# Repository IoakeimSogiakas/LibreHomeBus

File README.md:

## What’s New in Alpha

The project moves from Pre-Alpha to Alpha. The main change is that it now runs on a real RS-485 bus instead of a single board doing UART testing from Python.

Two CH32V003 nodes on a physical RS-485 bus, talking to a PC through a USB-RS485 dongle.
Discovery works on real hardware. Both nodes received unique addresses from the script.
The binary search is more forgiving of the timing on a real bus. A “no answer” now means three tries with no reply, and the result is checked afterwards: the lowest UID must answer and the number just below it must not. If the check fails, the search runs again.
Fixed CRC failures on the slave. Debug prints inside the frame polling loop were slow enough to corrupt frames on real RS-485. Per-frame logging is now behind a DEBUG_BUS switch in config.h, off by default.
Tested a switch (FID 1) driving a dimmer (FID 3) through both Home Assistant automations and ESPHome automations. The ESPHome version responds noticeably faster. The cause isn’t determined. The test setup has several hops (dongle, Windows, WSL, ESPHome host build, Home Assistant), and the extra latency might also be inherent to the Home Assistant path. This will be revisited with a real ESP master.
Scripts are being cut down. Only Descovery.py and bus_test.py will remain. bus_test.py is for bench testing nodes by hand.

## Why LibreHomeBus?

LibreHomeBus follows the architecture of professional centralized wired smart home systems like Loxone, but it is open source and costs far less.

Commercial setups can run to tens of thousands of dollars and often use proprietary bus encryption. In a home, fieldbus encryption adds little. To attack the bus, someone has to get into the house and open a wall. LibreHomeBus skips it in favor of simplicity, speed and low cost.

## 48V DC Room Topology 

A typical smart bulb contains its own AC-to-DC converter, so a house with fifty bulbs has fifty small mains power supplies. In cheap bulbs that converter sits right next to the LEDs in a sealed enclosure. The heat from the LEDs and the converter cooks its components, especially the electrolytic capacitors, and that is one of the most common ways LED bulbs fail.

LibreHomeBus does the AC-to-DC conversion once per room (or once per house) with a single power supply. That supply feeds a DC rail that runs next to the RS-485 data bus. Each node steps the rail down locally with a buck converter for the microcontroller and transceiver, and uses a dedicated LED driver for the light. The drivers sit apart from the LEDs, so the electronics stay cooler and last longer. Separating the driver from the LEDs is also common in good commercial lighting. This system just applies it throughout.

The rail is 48V for now, and the first prototype PCB will use it. It may change to 52V later. Earlier versions said 54V, and the power supply side is still untested, so treat the voltage as provisional.

A CH32V003 plus a proper LED driver makes a fixture with well-spaced, properly rated parts. The preliminary BOM for a custom SPI-based tunable white light is about €6.

*(Note: Schematics, BOMs, and Gerber files for the custom light fixtures and wall switches will be published in this repository as the hardware phase of the project matures.)*

---

# Project Status: Alpha

The firmware and discovery script work on a physical RS-485 bus with two nodes. This is still a prototype, and cleanup and refactoring are ongoing.

### Important Notes
* **Test setup:** Development is done with the ESPHome host build running in WSL, with the USB-RS485 dongle passed through with usbipd. A real ESP master hasn’t been tested yet.

* **Bus size:** Discovery has only been tested with two nodes. Larger multi-node buses are untested.

* **Scripts:** Two scripts remain in tools/. Descovery.py finds nodes, assigns addresses and writes a basic hub.yaml for ESPHome. bus_test.py is a menu for bench testing (read and write registers, on/off checks, identify LED test, watch a register, forget a node by UID). They work and can be used as they are, but they’re clunky. Settings like the serial port and ESPHome target are constants at the top of each file, and there is no command-line interface. A proper commissioning flow and a graphical interface are planned for the future.
* **Changing addresses:** There’s no separate script for it. Use the “forget a node by UID” option in bus_test.py to clear a node’s saved address, then run discovery again. Discovery picks the lowest free address, and you can’t choose one yourself yet. (I will probably add a way in the bus_test skript if I find a need for that)
* **ESPHome config generation:** Basic generation works for FID 1, 2, 3, 5 and 6. FID 4 has no YAML mapping yet and is skipped. Node identification and automation coupling are planned. See Future Plans.
* **PCB testing:** Not started. Everything so far runs on dev boards and breadboards. See Future Plans.

---

## Flavor Status

| FID | Personality | Registers Used | Interface | Status |
|:---:|:---|:---|:---|:---:|
| 1 | Toggle Switch Input | Reg 1 (State, read-only), Reg 2 (Identify LED) | Digital input, debounced with internal pull-up, PCB LED | RS-485 bus tested, LED bench tested |
| 2 | Relay / On-Off Light | Reg 1 (On/Off) | Push-pull digital output | RS-485 bus tested |
| 3 | Single-Channel Dimmer | Reg 1 (On/Off), Reg 2 (0..1000) | TIM1 CH1 PWM at 48 kHz | RS-485 bus tested |
| 4 | Tunable White (SPI) | Pending | Dedicated SPI driver IC | Pending |
| 5 | Tunable White (Dual PWM) | Reg 1 (On/Off), Reg 2 (Cold), Reg 3 (Warm) | TIM1 CH1 + CH3 PWM at 1 kHz | Bench tested |
| 6 | Wall Plug | Reg 1 (On/Off), Reg 2 (Identify LED) | Relay output, local toggle switch (no register), PCB LED | RS-485 bus tested |

Register 0 always holds the FID and is read-only. The identify LED register is only written by the commissioning script, and the node turns the LED off by itself after 30 s.

FID 4 is planned for bench testing next.

---

## Architecture & Hardware

```text
[ Home Assistant ]
       |
       |  Native API (Wi-Fi or Ethernet)
       v
[ ESPHome Master ] (ESP32 / ESP8266)
       |
       |  Modbus RTU (115200 baud, UART + DE/RE direction pin)
       v
======= RS-485 Bus ==============================================
       |                         |                         |
 [ CH32V003 Node ]         [ CH32V003 Node ]         [ CH32V003 Node ]
 Flavor 1 (Switch)         Flavor 2 (Relay)          Flavor 5 (TW Light)
==================================================================

```
---

### Why ESPHome as the Master?

Home Assistant's native Modbus integration relies on polling loops that are too sluggish for wall switches. Running the bus master on an ESP via ESPHome allows continuous, low-latency polling directly over the hardware UART. Input changes trigger immediate state pushes to Home Assistant over the native API.

### Hardware Notes
* **Transceivers & Voltage:** The system is currently designed and bench-tested around a **5V logic level** using the SN65HVD3082E RS-485 transceiver. Any standard 3.3V or 5V transceiver (MAX485, clones, isolated modules) is compatible, provided the logic levels match your supply rail.
* **Node Connections:** The CH32V003 slave firmware uses `PD5` for TX, `PD6` for RX, and `PD4` to control the transceiver's DE and /RE lines tied together.
* **Master Connections & Level Shifting:** The ESP requires three pins wired to its transceiver: UART TX, UART RX, and a GPIO driving DE and /RE. Since **all ESP32 and ESP8266 microcontrollers use 3.3V logic** (including ethernet gateways like the WT32-ETH01), if you are pairing the ESP with a 5V transceiver, you must step down the transceiver's 5V RX output to the ESP's 3.3V RX input using a simple voltage divider (e.g., a 2kΩ and 1kΩ resistor pair).

---

## Commissioning Protocol

New or unassigned nodes run with address 0 (`DEFAULT_ID = 0`). The discovery script uses a binary search across the 64-bit factory UID space, following a model similar to DALI commissioning:

1. **Compare (`0x41`):** The master broadcasts a UID threshold. Any unassigned node whose factory UID is less than or equal to that number answers with a single confirmation byte (`0x55`).

2. **Binary Search:** By halving the 64-bit UID search window based on whether anyone answers, the master isolates the lowest UID on the bus in roughly 64 queries.

3. **Assign Address (`0x42`):** Once a single chip is isolated, the master sends a broadcast command with that specific UID and its new address (1–247).

4. **Flash Storage:** The chip writes the new address into its last 64-byte flash page (`0x08003FC0`), so the address survives reboots and firmware reflashes.

5. **Clear / Reset (`0x43`):** Broadcast command that tells a specific UID to erase its saved address and revert to unassigned mode.

6. **Identification LED (switch and plug only):** The switch (FID 1) and plug (FID 6) flavors have an LED on `PC2`, controlled by register 2. Once a node has an address, the master can turn the LED on with a normal write (function `0x06`) so you can see which physical device got which address. It turns itself off after 30 seconds if the master forgets. The current discovery script doesn't use it yet, it's there for a later version.

---

## Future Plans
* **Node identification:** Before naming a node, the script asks which physical device it is. It uses the identify register on flavors that have one. On lights it can turn the light on.
* **Automation coupling:** Link inputs to outputs from the script, for example a switch to a specific light.
* **Better ESPHome YAML generation:** Read the discovered flavors, map the registers, and write a ready-to-flash config.
* **Caching:** The script will cache what it learns (for example the addresses, UIDs and flavors of nodes it has already found) so later runs are faster and don’t repeat the full discovery.
* **Real ESP master:** Move off the WSL host build and recheck latency, including the Home Assistant path. (this will probally happen in the next week)
* **PCB testing:** Prototype boards on the 48V rail. Planned for a few months from now.

## Licensing

This project is dual-licensed to cover both hardware designs and software/firmware components:

* **Firmware & Software Tools:** Licensed under [GNU General Public License v3.0 (GPL-3.0)](LICENSE).
* **Hardware (KiCad Schematics, PCB Layouts, & Libraries):** Licensed under [CERN-OHL-S v2 (Strong Reciprocal)](LICENSE-HARDWARE).

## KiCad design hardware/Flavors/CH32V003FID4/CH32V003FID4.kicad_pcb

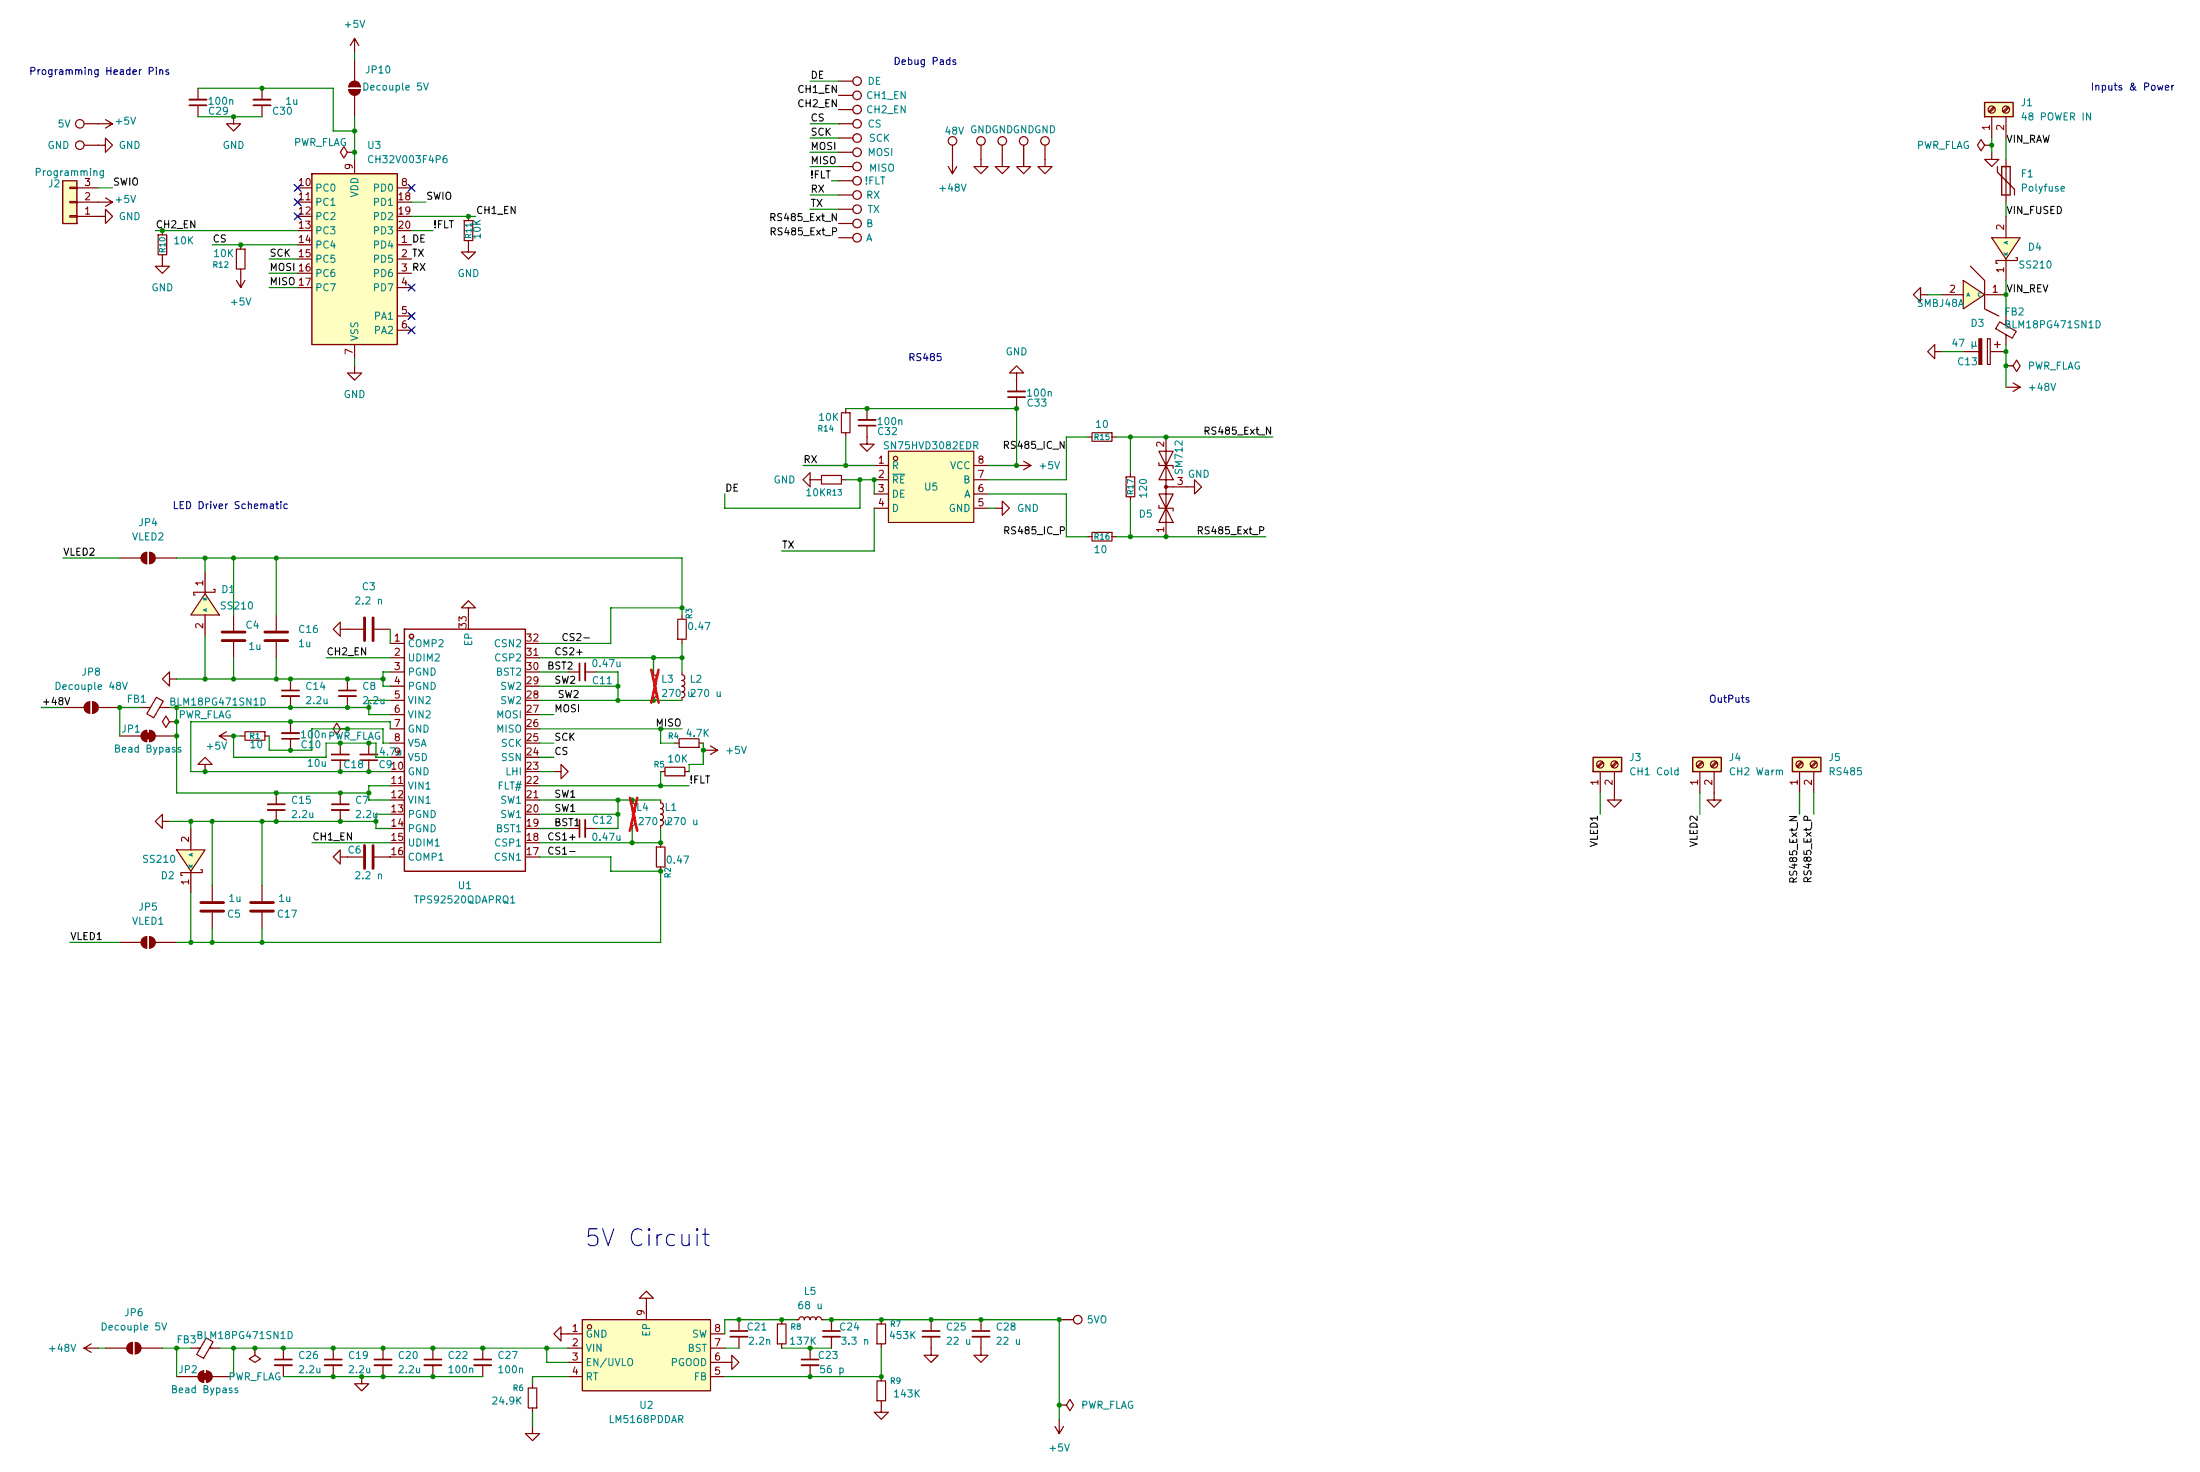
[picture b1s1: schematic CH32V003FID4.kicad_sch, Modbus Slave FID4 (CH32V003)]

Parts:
C3, C6: 2.2 n; C_1206_3216Metric
C4, C5, C16, C17, C30: 1u; C_1206_3216Metric
C7, C8, C14, C15, C19, C20, C26: 2.2u; C_1206_3216Metric
C9: 4.7u; C_1206_3216Metric
C10, C22, C27, C29, C32, C33: 100n; C_1206_3216Metric
C11, C12: 0.47u; C_1206_3216Metric
C13: 47 µ; CP_Elec_10x10.5
C18: 10u; C_1206_3216Metric
C21: 2.2n; C_1206_3216Metric
C23: 56 p; C_1206_3216Metric
C24: 3.3 n; C_1206_3216Metric
C25, C28: 22 u; C_1206_3216Metric
D1, D2, D4: SS210; D_SMA; MPN SS210; LCSC Part C14996
D3: SMBJ48A; SMB_L4.6-W3.6-LS5.3-RD; MPN SMBJ48A; LCSC Part C353356
D5: SM712; SOT-23; LCSC C5199207
F1: Polyfuse; Fuse_1812_4532Metric
FB1, FB2, FB3: BLM18PG471SN1D; L_0603_1608Metric
J1: 48 POWER IN; TerminalBlock_Phoenix_MKDS-1,5-2_1x02_P5.00mm_Horizontal
J2: Programming; PinHeader_1x03_P2.54mm_Vertical
J3: CH1 Cold; TerminalBlock_Phoenix_MKDS-1,5-2_1x02_P5.00mm_Horizontal
J4: CH2 Warm; TerminalBlock_Phoenix_MKDS-1,5-2_1x02_P5.00mm_Horizontal
J5: RS485; TerminalBlock_Phoenix_MKDS-1,5-2_1x02_P5.00mm_Horizontal
JP1, JP2: Bead Bypass; SolderJumper-2_P1.3mm_Bridged_RoundedPad1.0x1.5mm
JP4: VLED2; SolderJumper-2_P1.3mm_Open_RoundedPad1.0x1.5mm
JP5: VLED1; SolderJumper-2_P1.3mm_Open_RoundedPad1.0x1.5mm
JP6, JP10: Decouple 5V; SolderJumper-2_P1.3mm_Open_RoundedPad1.0x1.5mm
JP8: Decouple 48V; SolderJumper-2_P1.3mm_Open_RoundedPad1.0x1.5mm
L1, L2: 270 u; L_10.4x10.4_H4.8
L3, L4: 270 u; L_Bourns_SRR1260; not fitted
L5: 68 u; L_APV_ANR4020
R1, R15, R16: 10; R_0805_2012Metric
R2, R3: 0.47; R_0805_2012Metric
R4: 4.7K; R_0805_2012Metric
R5, R10, R11, R12, R13, R14: 10K; R_0805_2012Metric
R6: 24.9K; R_0805_2012Metric
R7: 453K; R_0805_2012Metric
R8: 137K; R_0805_2012Metric
R9: 143K; R_0805_2012Metric
R17: 120; R_0805_2012Metric
TP2: 5V; TestPoint_Pad_D1.5mm
TP3, TP12, TP13, TP14, TP15: GND; TestPoint_Pad_D1.5mm
TP4: CH2_EN; TestPoint_Pad_D1.5mm
TP5: CS; TestPoint_Pad_D1.5mm
TP6: SCK; TestPoint_Pad_D1.5mm
TP7: MOSI; TestPoint_Pad_D1.5mm
TP8: MISO; TestPoint_Pad_D1.5mm
TP9: CH1_EN; TestPoint_Pad_D1.5mm
TP10: !FLT; TestPoint_Pad_D1.5mm
TP11: 48V; TestPoint_Pad_D1.5mm
TP19: 5VO; TestPoint_Pad_D1.5mm
TP20: DE; TestPoint_Pad_D1.5mm
TP21: RX; TestPoint_Pad_D1.5mm
TP22: TX; TestPoint_Pad_D1.5mm
TP23: B; TestPoint_Pad_D1.5mm
TP24: A; TestPoint_Pad_D1.5mm
U1: TPS92520QDAPRQ1; MPN TPS92520QDAPRQ1; LCSC C3191125
U2: LM5168PDDAR; MPN LM5168PDDAR; LCSC Part C5751958
U3: CH32V003F4P6; TSSOP-20_4.4x6.5mm_P0.65mm; MPN CH32V003F4P6; LCSC C5187096
U5: SN75HVD3082EDR; MPN SN75HVD3082EDR; LCSC Part C140254

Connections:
+5V: C9.2, C18.2, C24.1, C25.1, C28.1, C32.2, C33.1, J2.2, JP10.2 (B), L5.2, R1.2, R4.1, R5.1, R7.2, R12.2, R14.1, TP2.1 (1_1), TP19.1 (1_1), U1.9 (V5D), U5.8 (VCC)
+48V: C13.1, FB2.2, JP6.1 (A), JP8.1 (A), TP11.1 (1_1)
/!FLT: R5.2, TP10.1 (1_1), U1.22 (FLT#), U3.20 (PD3)
/BST1: C12.1, U1.19 (BST1)
/BST2: C11.1, U1.30 (BST2)
/CH1_EN: R11.1, TP9.1 (1_1), U1.15 (UDIM1), U3.19 (PD2)
/CH2_EN: R10.1, TP4.1 (1_1), U1.2 (UDIM2), U3.13 (PC3)
/CS: R12.1, TP5.1, U1.24 (SSN), U3.14 (PC4)
/CS1+: L1.1, L4.1, R2.1, U1.18 (CSP1)
/CS1-: C5.1, C17.1, D2.1 (K), JP5.2 (B), R2.2, U1.17 (CSN1)
/CS2+: L2.1, L3.1, R3.1, U1.31 (CSP2)
/CS2-: C4.1, C16.1, D1.1 (K), JP4.2 (B), R3.2, U1.32 (CSN2)
/DE: R13.2, TP20.1 (1_1), U3.1 (PD4), U5.2 (~RE), U5.3 (DE)
/MISO: R4.2, TP8.1, U1.26 (MISO), U3.17 (PC7)
/MOSI: TP7.1, U1.27 (MOSI), U3.16 (PC6)
/RS485_Ext_N: D5.2 (A2), J5.1, R15.1, R17.1, TP23.1 (1_1)
/RS485_Ext_P: D5.1 (A1), J5.2, R16.1, R17.2, TP24.1 (1_1)
/RS485_IC_N: R15.2, U5.7 (B)
/RS485_IC_P: R16.2, U5.6 (A)
/RX: R14.2, TP21.1 (1_1), U3.3 (PD6), U5.1 (R)
/SCK: TP6.1, U1.25 (SCK), U3.15 (PC5)
/SW1: C12.2, L1.2, L4.2, U1.20 (SW1), U1.21 (SW1)
/SW2: C11.2, L2.2, L3.2, U1.28 (SW2), U1.29 (SW2)
/SWIO: J2.3, U3.18 (PD1)
/TX: TP22.1 (1_1), U3.2 (PD5), U5.4 (D)
/VIN_FUSED: D4.2 (A), F1.2
/VIN_RAW: F1.1, J1.2
/VIN_REV: D3.1 (C), D4.1 (K), FB2.1
/VLED1: J3.1, JP5.1 (A)
/VLED2: J4.1, JP4.1 (A)
GND: C3.1, C4.2, C5.2, C6.1, C7.2, C8.1, C9.1, C10.2, C13.2, C14.1, C15.2, C16.2, C17.2, C18.1, C19.2, C20.2, C22.2, C25.2, C26.2, C27.2, C28.2, C29.1, C30.1, C32.1, C33.2, D1.2 (A), D2.2 (A), D3.2 (A), D5.3 (common), J1.1, J2.1, J3.2, J4.2, R6.1, R9.1, R10.2, R11.2, R13.1, TP3.1 (1_1), TP12.1 (1_1), TP13.1 (1_1), TP14.1 (1_1), TP15.1 (1_1), U1.3 (PGND), U1.4 (PGND), U1.7 (GND), U1.10 (GND), U1.13 (PGND), U1.14 (PGND), U1.23 (LHI), U1.33 (EP), U2.1 (GND), U2.6 (PGOOD), U2.9 (EP), U3.7 (VSS), U5.5 (GND)
unnamed: C23.1, C24.2, R8.1
unnamed: FB1.1, JP1.1 (A), JP8.2 (B)
unnamed: C7.1, C8.2, C14.2, C15.1, FB1.2, JP1.2 (B), U1.5 (VIN2), U1.6 (VIN2), U1.11 (VIN1), U1.12 (VIN1)
unnamed: FB3.1, JP2.1 (A), JP6.2 (B)
unnamed: C19.1, C20.1, C22.1, C26.1, C27.1, FB3.2, JP2.2 (B), U2.2 (VIN), U2.3 (EN/UVLO)
unnamed: C29.2, C30.2, JP10.1 (A), U3.9 (VDD)
unnamed: C6.2, U1.16 (COMP1)
unnamed: C3.2, U1.1 (COMP2)
unnamed: C10.1, R1.1, U1.8 (V5A)
unnamed: C21.2, U2.7 (BST)
unnamed: C23.2, R7.1, R9.2, U2.5 (FB)
unnamed: R6.2, U2.4 (RT)
unnamed: C21.1, L5.1, R8.2, U2.8 (SW)

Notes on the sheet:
RS485
5V Circuit
Inputs & Power
Programming Header Pins
Debug Pads
LED Driver Schematic
OutPuts

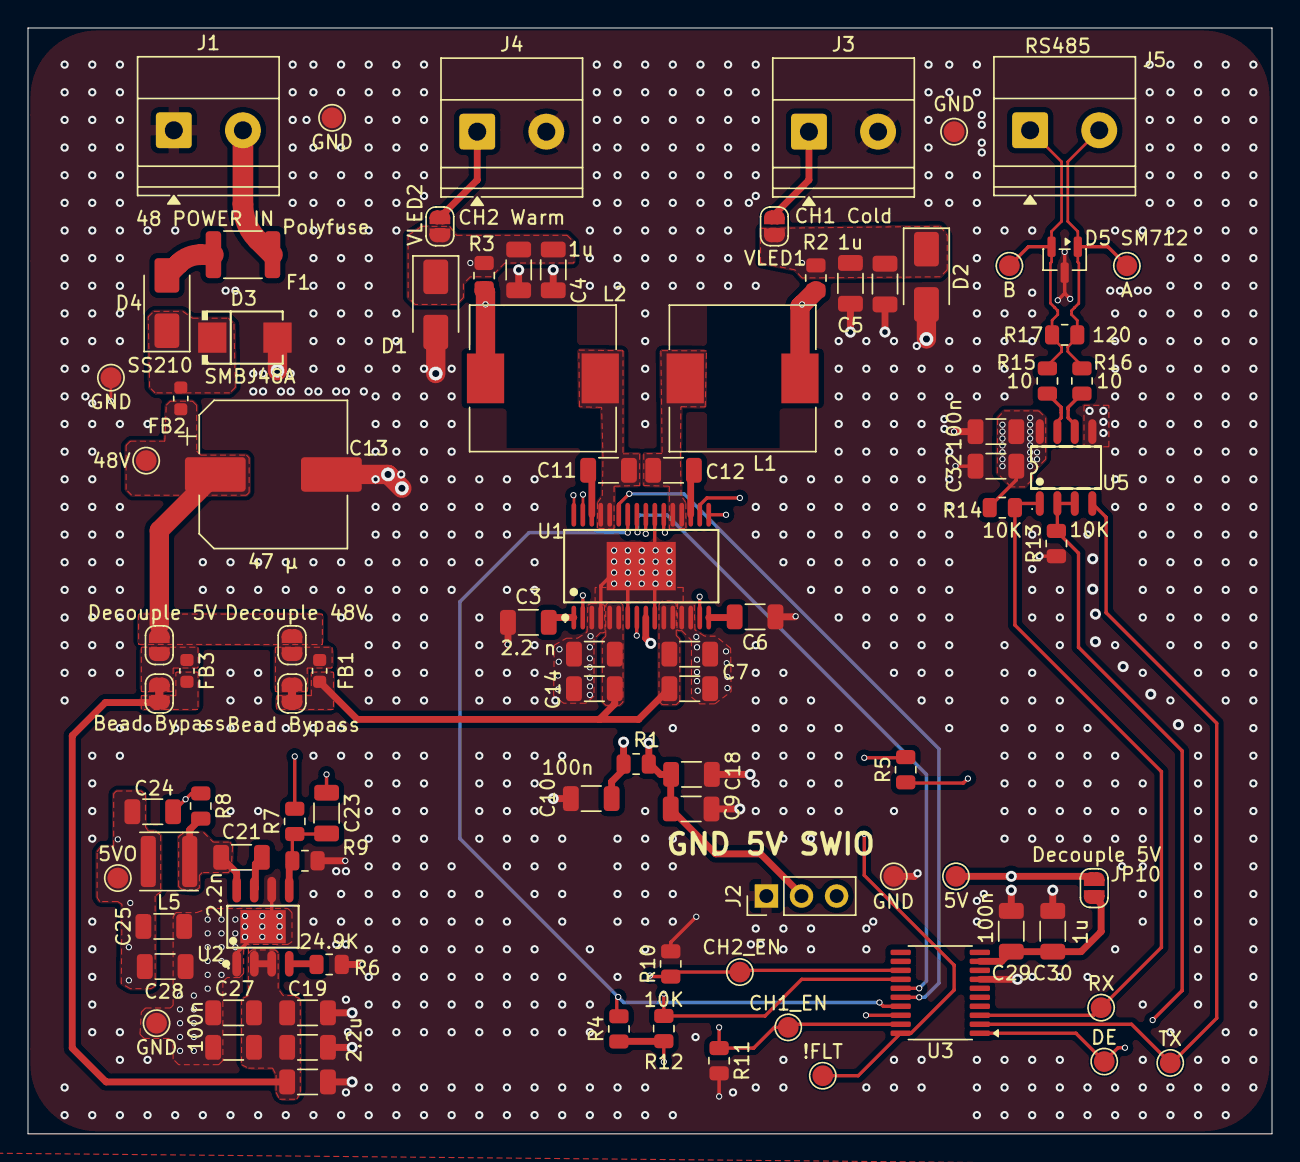
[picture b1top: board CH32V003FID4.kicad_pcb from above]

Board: 4 copper layers, 90.0 x 80.0 mm, 91 parts (0 on the bottom side), 44 nets.

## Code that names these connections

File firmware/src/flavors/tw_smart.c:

/*
 * FID 4: tunable white on a TPS92520-Q1. Same registers as FID 5.
 *   reg 1: on/off
 *   reg 2: cold 0..1000  (TPS channel 1)
 *   reg 3: warm 0..1000  (TPS channel 2)
 *
 * IADJ sets the LED current once at init, brightness is the TPS internal
 * PWM. CHx_EN drive UDIM and hard-gate each channel.
 *
 * Every pass sends at most one SPI frame (a read is two, ~50 us) so the
 * UART never misses a byte. Only tps_init() blocks longer (~1 ms).
 */

#include "node.h"
#include "tps92520.h"

#if FLAVOR == FID_TW_SMART

#define CH1_EN_PIN    PD2      /* UDIM1, cold */
#define CH2_EN_PIN    PC3      /* UDIM2, warm */
#define FLT_PIN       PD3      /* !FLT, open drain, active low */

#define RCS_MOHM      470      /* R2/R3, milliohm. Must match the board */
#define LED_MA        340      /* LED current per channel */
#define TON           7        /* ~437 kHz switching */
#define PWMDIV        0        /* 1507 Hz PWM */

#define REG_ONOFF     1
#define REG_COLD      2
#define REG_WARM      3
#define LEVEL_MAX     1000

#define STATUS_MS     200
#define RETRY_MS      500

/* I_LED = 2.45 V * IADJ / 1024 / (14 * Rcs) */
#define IADJ  ((LED_MA * 14ULL * RCS_MOHM * 1024 + 1225000) / 2450000)

#if IADJ > 1023
#error "LED_MA is above what RCS_MOHM allows"
#endif
#if LED_MA > 1600
#error "TPS92520 is rated 1.6 A per channel"
#endif

static const uint8_t en_pin[2]  = { CH1_EN_PIN, CH2_EN_PIN };
static const uint8_t pwm_l[2]   = { TPS_CH1PWML, TPS_CH2PWML };
static const uint8_t pwm_h[2]   = { TPS_CH1PWMH, TPS_CH2PWMH };

static uint8_t  ready;
static uint16_t cur[2];        /* duty the TPS has */
static uint8_t  step[2];       /* 0 idle, 1 high byte sent */
static uint16_t next[2];
static uint8_t  st_step;
static uint8_t  last_s1, last_s2, last_tw;
static uint32_t t_status, t_retry;

static uint16_t duty(uint16_t level)
{
    return (uint16_t)(((uint32_t)level * TPS_PWM_MAX + LEVEL_MAX / 2) / LEVEL_MAX);
}

static void stop(void)
{
    funDigitalWrite(CH1_EN_PIN, FUN_LOW);
    funDigitalWrite(CH2_EN_PIN, FUN_LOW);
    ready = 0;
    t_retry = SysTick->CNT;
}

static void start(void)
{
    if (!tps_init(IADJ, IADJ, TON, PWMDIV)) {
        t_retry = SysTick->CNT;
        return;
    }
    ready = 1;
    cur[0] = cur[1] = 0;
    step[0] = step[1] = 0;
    st_step = 0;
    t_status = SysTick->CNT;
    debugln("tps ready, iadj %u", (unsigned)IADJ);
}

/* One SPI frame per call. Returns 1 if it used the bus. */
static int channel_poll(int ch, uint16_t want)
{
    if (step[ch] == 0) {
        if (want == cur[ch]) return 0;
        if (want == 0) funDigitalWrite(en_pin[ch], FUN_LOW);
        next[ch] = want;
        tps_write(pwm_h[ch], next[ch] >> 8);
        step[ch] = 1;
        return 1;
    }
    tps_write(pwm_l[ch], next[ch] & 0xFF);     /* low byte latches the value */
    cur[ch] = next[ch];
    step[ch] = 0;
    if (cur[ch]) funDigitalWrite(en_pin[ch], FUN_HIGH);
    return 1;
}

static void status_poll(void)
{
    int v;

    switch (st_step) {
    case 0:
        if ((uint32_t)(SysTick->CNT - t_status) < STATUS_MS * DELAY_MS_TIME) return;
        t_status = SysTick->CNT;
        v = tps_read(TPS_STATUS3);
        if (v < 0 || (v & (TPS_STANDALONE | TPS_PC | TPS_CMWTO))) {
            debugln("tps lost (status3 %d), restarting", v);
            stop();
            return;
        }
        if (!!(v & TPS_TW) != last_tw) {
            last_tw = !!(v & TPS_TW);
            debugln("tps thermal warning %s", last_tw ? "on" : "off");
        }
        if ((v & (TPS_CH1STATUS | TPS_CH2STATUS)) || !funDigitalRead(FLT_PIN)) {
            st_step = 1;
        }
        return;
    case 1:
        v = tps_read(TPS_STATUS1);
        if (v >= 0 && v != last_s1) {
            last_s1 = v;
            debugln("tps status1 %02X", v);
        }
        st_step = 2;
        return;
    case 2:
        v = tps_read(TPS_STATUS2);
        if (v >= 0 && v != last_s2) {
            last_s2 = v;
            debugln("tps status2 %02X", v);
        }
        st_step = 3;
        return;
    default:
        tps_write(TPS_SYSCFG1, TPS_CMWEN | TPS_CH1INTPWM | TPS_CH1EN |
                               TPS_CH2INTPWM | TPS_CH2EN | TPS_FPINRST);
        st_step = 0;
        return;
    }
}

void flavor_init(void)
{
    funPinMode(CH1_EN_PIN, GPIO_CFGLR_OUT_10Mhz_PP);
    funPinMode(CH2_EN_PIN, GPIO_CFGLR_OUT_10Mhz_PP);
    funDigitalWrite(CH1_EN_PIN, FUN_LOW);
    funDigitalWrite(CH2_EN_PIN, FUN_LOW);
    funPinMode(FLT_PIN, GPIO_CFGLR_IN_PUPD);
    funDigitalWrite(FLT_PIN, FUN_HIGH);

    regs[REG_ONOFF] = 0;
    regs[REG_COLD]  = LEVEL_MAX;
    regs[REG_WARM]  = LEVEL_MAX;
    reg_max[REG_ONOFF] = 1;
    reg_max[REG_COLD]  = LEVEL_MAX;
    reg_max[REG_WARM]  = LEVEL_MAX;

    tps_spi_init();
    start();            /* must run within ~1.5 s of TPS power-up */
}

void flavor_poll(void)
{
    if (!ready) {
        /* tps_init blocks ~1 ms, don't start it while a frame is coming in */
        if (rx_len == 0 &&
            (uint32_t)(SysTick->CNT - t_retry) > RETRY_MS * DELAY_MS_TIME) {
            start();
        }
        return;
    }

    uint16_t on = regs[REG_ONOFF];
    uint16_t want0 = on ? duty(regs[REG_COLD]) : 0;
    uint16_t want1 = on ? duty(regs[REG_WARM]) : 0;

    if (step[1] == 0 && channel_poll(0, want0)) return;
    if (channel_poll(1, want1)) return;
    status_poll();
}

#endif /* FLAVOR == FID_TW_SMART */

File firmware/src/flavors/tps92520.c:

/*
 * TPS92520-Q1 dual buck LED driver over SPI1.
 *
 * Frame (16 bit, MSB first, mode 0):  CMD | A5..A0 | PAR | D7..D0
 *   CMD 1 = write, PAR makes the number of 1s odd.
 * The reply to a frame comes back during the next one.
 */

#include "tps92520.h"

#if FLAVOR == FID_TW_SMART

#define CS_PIN     PC4
#define SCK_PIN    PC5
#define MOSI_PIN   PC6
#define MISO_PIN   PC7      /* open drain on the TPS side, needs a pull-up */

/* 48 MHz / 64 = 750 kHz. Datasheet max is 2 MHz; MISO rises through the
 * pull-up, so leave margin. */
#define SPI_DIV    SPI_BaudRatePrescaler_64

#define RD_MASK    0xFC00   /* SPE + the fixed 11000 field */
#define RD_OK      0x6000

void tps_spi_init(void)
{
    RCC->APB2PCENR |= RCC_APB2Periph_SPI1;

    funPinMode(CS_PIN, GPIO_CFGLR_OUT_10Mhz_PP);
    funDigitalWrite(CS_PIN, FUN_HIGH);
    funPinMode(SCK_PIN, GPIO_CFGLR_OUT_10Mhz_AF_PP);
    funPinMode(MOSI_PIN, GPIO_CFGLR_OUT_10Mhz_AF_PP);
    funPinMode(MISO_PIN, GPIO_CFGLR_IN_PUPD);
    funDigitalWrite(MISO_PIN, FUN_HIGH);

    SPI1->CTLR1 = SPI_Direction_2Lines_FullDuplex | SPI_Mode_Master |
                  SPI_DataSize_16b | SPI_CPOL_Low | SPI_CPHA_1Edge |
                  SPI_NSS_Soft | SPI_DIV | SPI_FirstBit_MSB;
    SPI1->CTLR1 |= CTLR1_SPE_Set;
}

static uint16_t xfer(uint16_t out)
{
    funDigitalWrite(CS_PIN, FUN_LOW);
    Delay_Us(1);
    (void)SPI1->DATAR;
    while (!(SPI1->STATR & SPI_STATR_TXE));
    SPI1->DATAR = out;
    while (!(SPI1->STATR & SPI_STATR_RXNE));
    uint16_t in = SPI1->DATAR;
    while (SPI1->STATR & SPI_STATR_BSY);
    Delay_Us(1);
    funDigitalWrite(CS_PIN, FUN_HIGH);
    Delay_Us(2);
    return in;
}

static uint16_t frame(uint8_t wr, uint8_t addr, uint8_t data)
{
    uint16_t f = ((uint16_t)(wr ? 1 : 0) << 15) | ((uint16_t)(addr & 0x3F) << 9) | data;
    uint16_t p = f;
    p ^= p >> 8;
    p ^= p >> 4;
    p ^= p >> 2;
    p ^= p >> 1;
    if (!(p & 1)) f |= 1u << 8;
    return f;
}

int tps_read(uint8_t addr)
{
    xfer(frame(0, addr, 0));
    uint16_t r = xfer(frame(0, TPS_SYSCFG1, 0));
    if ((r & RD_MASK) != RD_OK) return -1;
    return r & 0xFF;
}

void tps_write(uint8_t addr, uint8_t data)
{
    xfer(frame(1, addr, data));
}

/* Write, then check the echo the TPS sends back in the next frame. */
static int write_check(uint8_t addr, uint8_t data)
{
    uint16_t f = frame(1, addr, data);
    xfer(f);
    uint16_t r = xfer(frame(0, TPS_SYSCFG1, 0));
    uint16_t want = ((f >> 1) & 0x7F00) | data;
    return r == want;
}

static int write_iadj(uint8_t reg_l, uint16_t v)
{
    return write_check(reg_l + 1, v >> 2) && write_check(reg_l, v & 3);
}

int tps_init(uint16_t iadj1, uint16_t iadj2, uint8_t ton, uint8_t pwmdiv)
{
    const uint8_t run = TPS_CMWEN | TPS_CH1INTPWM | TPS_CH1EN | TPS_CH2INTPWM | TPS_CH2EN;

    int s3 = tps_read(TPS_STATUS3);
    if (s3 < 0) {
        s3 = tps_read(TPS_STATUS3);     /* TPS may still be coming out of POR */
        if (s3 < 0) return 0;
    }
    if (s3 & TPS_STANDALONE) {
        tps_write(TPS_RESET, 0xC3);
        if (tps_read(TPS_STATUS3) < 0) return 0;
    }

    if (iadj1 > 1023) iadj1 = 1023;
    if (iadj2 > 1023) iadj2 = 1023;

    return write_check(TPS_SYSCFG1, TPS_CMWEN) &&
           write_check(TPS_SYSCFG2, 0) &&
           write_check(TPS_PWMDIV, pwmdiv) &&
           write_check(TPS_CH1TON, ton) &&
           write_check(TPS_CH2TON, ton) &&
           write_iadj(TPS_CH1IADJL, iadj1) &&
           write_iadj(TPS_CH2IADJL, iadj2) &&
           write_check(TPS_CH1PWMH, 0) && write_check(TPS_CH1PWML, 0) &&
           write_check(TPS_CH2PWMH, 0) && write_check(TPS_CH2PWML, 0) &&
           write_check(TPS_LHCFG1, 0) &&
           write_check(TPS_SYSCFG1, run) &&
           (tps_write(TPS_SYSCFG1, run | TPS_FPINRST), 1);
}

#endif /* FLAVOR == FID_TW_SMART */
